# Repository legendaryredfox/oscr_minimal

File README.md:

# oscr_minimal — dumper de cartuchos SNES / NES / Famicom / Mega Drive / GBA

*English summary: [`README.en.md`](README.en.md).*

Shield para **Arduino Mega 2560 (R3)** que lê ROMs e saves de cartuchos pela USB, direto para o PC.
Sem LCD, sem cartão SD. Somente um cartucho por vez.

> **Estado:** 12 placas com projeto KiCad e gerbers, firmware (fork do OSCR com protocolo serial), CLI Python, CLI e GUI em Kotlin (pt-BR, en, ru, zh). **Nenhuma placa foi montada e nada foi testado com cartucho real**: só os testes automáticos no PC, as verificações de hardware abaixo e, em 2026-11-21, a primeira execução num Mega sem shield (`docs/referencia/teste-de-bancada.md`) rodaram. Ver "O que foi testado e o que falta".

## Atribuição

Baseado no **Open Source Cartridge Reader (OSCR)** de sanni e comunidade.

- Hardware original: <https://github.com/sanni/cartreader> (licença **CC BY 4.0**).
  Upstream atual: <https://github.com/oscartreader>.
- Firmware original: GPL v3. O firmware deste projeto continuará GPL v3.
- Slots (símbolos e footprints) copiados do OSCR, com alterações descritas em `boards/_lib/README.md`.

Adaptado por: <https://github.com/legendaryredfox/oscr_minimal>

## Diferenças em relação ao OSCR original

Este projeto não é uma reimplementação: o firmware é o do OSCR e as placas mantêm a pinagem dele. O que muda é **onde fica a interface** (no computador, não no aparelho) e **o tamanho do hardware**.

| | OSCR original | Este projeto |
|---|---|---|
| **Uso** | Aparelho independente: tela LCD, botão rotativo e cartão SD; o PC é opcional | Só com o computador: controle e arquivos pela USB. **Sem LCD, sem botões, sem cartão SD, sem RTC** |
| **Onde vão ROM e save** | Para arquivos no cartão SD | Direto para o PC por um protocolo serial binário (quadros com CRC32, blocos com ACK, 1.000.000 baud, com recuo para 500.000 e 115.200); o firmware nunca guarda arquivo |
| **Placa** | HW5: placa SMD com o módulo Mega Pro embutido e todos os slots | Shield **100 % THT** sobre um **Arduino Mega 2560 R3** comum, soldável à mão; várias variantes por combinação de sistemas (`boards/README.md`), da mínima de dois slots à completa |
| **Pinagem** | HW5 | **Idêntica**: cada sinal de cada slot vai para o mesmo pino do Mega, e por isso os núcleos de leitura do OSCR rodam sem alteração (`boards/<placa>/docs/pinmap.md` guarda a tabela cruzada com o OSCR) |
| **Tensão dos slots** | Chave 3,3 V / 5 V e VSELECT | 5 V fixo nos slots SNES, NES, Famicom, Mega Drive e Master System; 3,3 V nos slots GBA e N64 (regulador próprio). Algumas versões recentes de placa têm seletor 3,3 V / 5 V opcional, com trava por jumper. O 5 V **não** é desligado por software |
| **Relógio e CIC** | Si5351 e CIC conforme a versão da placa | Módulo Si5351 em header fêmea; CIC do SNES em PIC12F629 num soquete da própria placa (a alternativa com RP2040 está planejada e ainda não foi validada) |
| **Menus e botões** | Menus no LCD | O laço de comandos do protocolo (`firmware/oscr/src/dumper/`) chama as funções dos núcleos direto, **sem menu**; erros fatais e esperas por botão voltam ao laço em vez de travar |
| **Identificação do jogo** | Banco CRDB no SD | No PC: bases No-Intro e NES 2.0 (CRC32, SHA-1), busca e nome do arquivo pelo jogo (`--db`, `--game`) |
| **Segurança de gravação** | Pelo menu | O PC faz backup do save antes de gravar, relê e compara depois, pede confirmação e recusa tamanhos que não cabem no chip |
| **Interface** | Tela e botões | CLI em Python, CLI em Kotlin (mesmo contrato, saída JSON para scripts e agentes) e GUI em Kotlin para Linux, macOS e Windows (pt-BR, en, ru, zh) |
| **Gravar o firmware** | Ferramentas do upstream | `dumper firmware-flash` ou o cartão da GUI; com a placa escolhida o programa confere o firmware, grava o perfil da placa na EEPROM e, se faltar suporte, grava a imagem certa depois de pedir confirmação |

### Firmware: o que é do OSCR e o que é daqui

- **Base:** o firmware novo do OSCR (`vendor/oscr/firmware`), copiado para `firmware/oscr/`. Quem escolhe os núcleos é o `user.ini`: SNES (com Sufami Turbo, GPC, Satellaview e SF Memory), NES/Famicom, Mega Drive, Master System, N64, GB/GBC/GBA, programador de flash e o autoteste, mais 19 outros sistemas por adaptador no slot SNES (F-20: Atari 2600/5200/7800/8 bits/Lynx/Jaguar, ColecoVision, Neo Geo Pocket, Vectrex, Arcadia 2001, RCA Studio II, Tomy Pyuuta, Supervision, PV-1000, Bally Astrocade, Channel F, Odyssey 2, Pokémon Mini e V.Smile; adaptadores ainda não desenhados, `docs/planos/adaptadores.md`). Os outros consoles do upstream (por exemplo Commodore 64 e PC Engine) **não estão ligados** (`docs/planos/pendencias.md`).
- **Regra do projeto:** chamar a função do OSCR direto e escrever código próprio só nas costuras. Onde divergimos, o motivo está em `docs/decisoes.md`.
- **Código só daqui** (`firmware/oscr/src/dumper/`): o protocolo e a sessão; o `StreamFile`, arquivo virtual que no lugar do SD manda os bytes pela serial; o laço de comandos; o perfil da placa (`BOARD`, na EEPROM); o comando de tensão (`VOLT`); a calibração do Si5351 (`CLOCK`, guardada na EEPROM, no lugar do arquivo `snes_clk.txt` do SD); e o `SELFTEST`.
- **Remendos no upstream:** poucos e marcados com `OSCR_DUMPER` ou "fork": o tipo do arquivo e do `sd` em `Storage`, a UI de texto muda (`ClockedSerial.mute`), os tratamentos de erro e de `waitButton` do `ascii.cpp` e o `main.cpp` (laço próprio no lugar do menu).
- **Baud:** 1.000.000, contra 250.000 do upstream, definido pelo `monitor_speed` da placa `mega-embed` no `user.ini`.
- **Limites conhecidos do fluxo serial:** só existe leitura sequencial (sem `seek`), e o que o núcleo relê para conferir um save gravado devolve 0 bytes; por isso a conferência fica a cargo do PC, que relê depois de gravar.
- Mapa completo e estado: `docs/referencia/fork-oscr.md`. Cada função do OSCR e onde ela mora aqui: `docs/referencia/funcoes-oscr.md`.

### O que isto **não** substitui

- O OSCR original tem anos de uso e de cartuchos reais. **Este fork quase não tem validação em hardware:** em 2026-11-21 rodou pela primeira vez, num Mega sem shield e sem cartucho, e essa primeira execução achou e corrigiu vários problemas, de baud errado a gravação de firmware que travava (D196 a D199). **Nenhuma leitura de cartucho real foi feita ainda.** Os núcleos do OSCR são os de sempre, mas o que está em volta (protocolo, placas, sequência de chamadas) é novo.
- Quem quer um leitor autônomo, sem computador, deve usar o OSCR original.
- Funções do OSCR que ainda faltam aqui: `docs/referencia/funcoes-oscr.md`.

## Conteúdo

| Pasta | O que tem |
|---|---|
| `CLAUDE.md` | Decisões de projeto e fases (também serve de instrução para assistentes de código) |
| `boards/` | **Variantes de hardware**, uma pasta cada (índice e estado em `boards/README.md`). Com projeto KiCad e gerbers: `16_and_8_bits/` (5 slots), `16_bits/` (SNES e Mega Drive) e as de um sistema só ou de dois: `megadrive/`, `snes/`, `nes/`, `famicom/`, `famicom_nes/`, `8_bits/` (NES, Famicom e Master System), `gb_gba/`, `completa/` (sete slots) |
| `boards/<placa>/docs/pinmap.md` | **Fonte da verdade** de cada placa: pino do slot → pino do Mega (o da `16_and_8_bits` é gerado por `tools/gen_pinmap.py`; os das outras são recortes dele) |
| `docs/decisoes.md` | Log de decisões, desvios e pendências |
| `boards/<placa>/hardware-<versão>/` (uma pasta por versão), `fab/`, `docs/` | Projeto KiCad 10 (`dumper.kicad_pro/_sch/_pcb`), gerbers e zip da JLCPCB (`fab/PEDIDO.md` diz como pedir) e `bom.md`/`montagem.md` de cada placa |
| `boards/_lib/` | Símbolos e footprints KiCad compartilhados entre as variantes |
| `docs/referencia/uso.md` | **Guia de uso**: casos de uso, cenários por sistema e solução de problemas |
| `docs/referencia/protocolo.md`, `docs/referencia/cli.md`, `docs/referencia/fork-oscr.md`, `docs/referencia/funcoes-oscr.md`, `docs/referencia/limites.md` | Protocolo serial, guia da CLI, o que o fork muda no OSCR, inventário das funções do OSCR e limites conhecidos |
| `docs/planos/` | O que ainda não foi feito: `pendencias.md` (ids e o que falta), `adaptadores.md` (adaptadores da F-20), `melhorias-megadrive.md`, `placa-v1.3-rp2040.md` |
| `docs/planos/placa-v1.3-rp2040.md`, `firmware/cic_rp2040/` | CIC do SNES com RP2040-Zero no lugar do PIC (ainda não validado; as placas atuais usam o PIC12F629) |
| `firmware/`, `host/`, `gui/` | Comuns a todas as variantes |
| `database/oscr/` | Base de jogos (24 007, CRC32) do OSCR legado, GPL v3, mais `json/` (bases do `oscr-databases`, 4,9 mil CRC32 novos; o repositório de origem não declara licença, D127); carregada sozinha pelo host e pela GUI (D88, D127) |
| `tools/` | Scripts de hardware: `check_netlist.py` (`--board <placa>`), `export_fab.sh`, `gen_pinmap.py`, `build_lib.py`, `fill_zones.py` e os de cada placa (`megadrive/`, `snes/`, `nes/`, `famicom/`, `famicom_nes/`, `gb_gba/`, `revisao/`); ver `tools/README.md` |

## Adaptadores e repositórios de referência

O código de leitura dos cartuchos vem do OSCR; o que muda por sistema é o adaptador. Fontes consultadas e adaptadores que o firmware reconhece (D136, D137):

| Referência | Para quê |
|---|---|
| <https://github.com/sanni/cartreader> (pasta `hardware/`: `mastersystem_adapter`, `six_slot_adapter`, `*_adapter`) | KiCad dos adaptadores do OSCR; o slot Master System da `megadrive_sms` e os footprints dos slots vêm daí (CC BY 4.0). Arquivado desde 2026-06 |
| <https://github.com/oscartreader/oscr-firmware> | firmware atual do OSCR (GPL v3), base do fork em `firmware/oscr/` |
| <https://github.com/oscartreader/oscr-databases> | bases de jogos e a tabela de chips de flash (`database/oscr/`, D127 e D135; sem licença declarada) |
| <https://github.com/oscartreader/oscr-hardware> | repositório de hardware do novo upstream (vazio em 2026-11-08) |
| <https://github.com/sanni/cartreader/discussions/874> | discussão do adaptador de Game Gear (slot com o conector do RetroSix) |
| <https://www.raphnet.net/electronique/sms_cartridge_programmer/index_en.php> | adaptador **Raphnet** de Master System / SG-1000 (modo `SMSRaphnet` e `SG1000Raphnet` do `SMS.cpp`) |
| <https://forum.retrode.com> | adaptadores **Retrode** (`SMSRetrode`, `GGRetrode` do `SMS.cpp`) |
| <https://www.retrosix.wiki> | pinagem do cartucho de Game Gear e de outros consoles Sega |
| <https://www.smspower.org/maxim/Documents/Pinouts> | pinagem do conector de cartucho do Master System, Mark III e SG-1000 |

**Game Gear e SG-1000** não têm slot próprio nas placas deste projeto: usam adaptador no slot Mega Drive (Retron 3in1, Retrode, Raphnet). Os adaptadores que achei são comerciais; **não encontrei arquivos abertos** (KiCad) deles. Se aparecer um adaptador de código aberto, acrescente o link aqui.

**Tensão dos adaptadores (D138).** Os slots são de 5 V; os flashcarts comuns de Mega Drive e Master System precisam disso (regulam 3,3 V por dentro). As placas v1.1 de Mega Drive, SMS, NES e Famicom têm o **seletor 3,3 V/5 V** (padrão 5 V, `--voltage 3v3` para 3,3 V, alerta ao passar de 3,3 V para 5 V) e o jumper J1 \"TRAVA 3,3 V\"; todas as placas têm o fusível F1 (5×20 mm, 500 mA, em suporte de clipes, troca sem solda) opcional. Adaptador de Game Gear ou cartucho de 3,3 V: confira a tensão do adaptador antes de ligar. Detalhes: `docs/decisoes.md` D138.

## Aviso

- **Use por sua conta e risco.** Hardware e software saem sem garantia (CC BY 4.0 e GPL v3). Placas e firmware são experimentais.
- **Um cartucho por vez.** As placas levam 5 V aos slots de SNES, NES, Famicom, Mega Drive e Master System; os slots GBA e N64 são 3,3 V (regulador próprio), e as versões com seletor de tensão podem pôr o slot em 3,3 V. Desligue o USB antes de trocar de cartucho e **não use adaptador de GB/GBA** em placa sem o slot GBA.
- **Gravar ROM apaga o chip**, e abortar no meio deixa o chip pela metade. Faça backup do save antes de gravar e comece por cartuchos sem valor (`docs/referencia/uso.md`, seção 7).
- **Uso legal.** A ferramenta serve para fazer cópia de segurança dos cartuchos que você possui. Este repositório não distribui ROMs, BIOS nem chaves; `database/oscr/` só tem listas de nomes e CRC32 do OSCR.
- Nintendo, Super Nintendo, Famicom, Game Boy, Sega, Mega Drive e outros nomes são marcas dos seus donos, citadas só para dizer com o que o projeto é compatível. Sem vínculo com essas empresas nem com o projeto OSCR.

## O que foi testado e o que falta

Cobertura medida (Python 90 %, Kotlin 91,7 % das linhas, C++ puro no PC) e o que nenhum teste alcança: [`docs/referencia/cobertura-testes.md`](docs/referencia/cobertura-testes.md).

**Testado no PC (2026-11-27, D228):** host Python (`cd host && python3 -m pytest -q`, 478 testes), firmware (`make -C firmware/oscr/pc-tests test`, 26 binários de protocolo e regras puras; `pio run -e SerialASCII` compila, 77 % do flash), GUI e CLI Kotlin (`cd gui && ./gradlew :shared:jvmTest :desktopApp:compileKotlin :cliApp:compileKotlin`; a janela abre em display virtual, `tools/gui_smoke.sh`), as 12 placas em 22 versões (`python3 tools/check_all_boards.py`: ERC, DRC sem ligação aberta, netlist contra o `pinmap.md`, silk e SHA-256 dos zips; 0 erros na D191) e as tabelas dos adaptadores (`tools/check_adaptador_*.py`). O CI (`.github/workflows/ci.yml`) nunca executou.

**Em hardware:** só um Mega sem shield, sem Si5351 e sem cartucho (2026-11-21, D196 a D199: baud, gravação do firmware pela GUI, autoteste, perfil da placa). Cinco PIC12F629 gravados e conferidos por leitura, nenhum testado num cartucho (D214, D220).

**Falta:** montar uma placa e fazer o primeiro dump comparando o CRC32 com o No-Intro (roteiro na seção 7 de `docs/referencia/uso.md` e em `docs/referencia/teste-de-bancada.md`); conferir as medidas dos slots e do Si5351, o lado da etiqueta e os espaçadores com as peças reais; revisar à mão no KiCad os layouts do autoroteador; desenhar os adaptadores da F-20; serial a 1.000.000 baud em macOS e Windows; revisão das traduções ru e zh; dmg e msi. A única placa encomendada é a `16_bits` v1.0 original. Lista completa e o que falta do OSCR: `docs/planos/pendencias.md` e `docs/referencia/funcoes-oscr.md`.

## CIC do SNES: alternativas ao chip de 8 pinos

As placas com SNES usam hoje o **PIC12F629** (DIP-8, em soquete, gravado com o `snescic-lock-resync.hex` do OSCR). Estamos **estudando alternativas ao CIC de 8 pinos**; a mais avançada é um RP2040-Zero que roda o mesmo programa num interpretador (`docs/planos/placa-v1.3-rp2040.md`, `firmware/cic_rp2040/`, D89). Nada disso foi validado em hardware, e o PIC continua sendo o caminho suportado.

## Verificação

```
python3 tools/check_netlist.py --board <placa>        # netlist do esquemático vs boards/<placa>/docs/pinmap.md
kicad-cli sch erc boards/<placa>/hardware-<versão>/dumper.kicad_sch                # ERC
kicad-cli pcb drc --schematic-parity boards/<placa>/hardware-<versão>/dumper.kicad_pcb   # DRC
python3 tools/check_all_boards.py                     # todas as placas e versões de uma vez
tools/export_fab.sh <placa> <versão>                  # gerbers, furos, BOM e zip em boards/<placa>/fab/
```

## Recriar o `vendor/` (não versionado)

```
mkdir -p vendor/oscr && cd vendor/oscr
git clone --depth 1 https://github.com/sanni/cartreader legacy
git clone --depth 1 https://github.com/oscartreader/oscr-firmware firmware
```

`tools/gen_pinmap.py` lê `vendor/oscr/legacy/` (pinout.ods, esquemáticos KiCad, firmware).

## Contribuir

Veja `CONTRIBUTING.md`. Testes em hardware são o que mais ajuda: abra uma issue com o modelo "Teste em hardware" (placa, cartucho, versão, logs).

## Requisitos

KiCad 10.0.8 (`kicad-cli`), Python 3.11+. Para refazer layouts: o servidor MCP do KiCad (Python com `pcbnew`) e o Freerouting; ver `tools/README.md` e `docs/decisoes.md` (D92 a D101).

## Licença

Hardware: **CC BY 4.0**. Software: **GPL v3 ou posterior**. Mesmas licenças do OSCR; ver `LICENSE.md`.

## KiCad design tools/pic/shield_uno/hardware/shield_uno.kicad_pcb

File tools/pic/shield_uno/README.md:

# Programador de PIC12F629 em shield para Arduino Uno

Grava o **PIC12F629** (o CIC "lock" do SNES SA-1, `snescic-lock-resync.hex`) com um Arduino Uno e o
[ardpicprog](https://rweather.github.io/ardpicprog/). Resolve o problema de quem não tem PICkit: o 12F629 só grava
com Vpp de uns 12 a 13 V no MCLR, e o CH341A não gera isso.

Este shield é o circuito do ardpicprog para o PIC12F629 em DIP-8 direto (a ligação já descrita em
[`../uno/README.md`](../uno/README.md), D91), desenhado em KiCad. Há três jeitos de montar o mesmo circuito, na ordem
de comodidade: **A.** PCB do shield (este projeto KiCad), **B.** protoboard, **C.** placa perfurada.

> **Estado (2026-11-25):** v1.1 (pinos D8/D9/D10). **Nada foi encomendado**, e nem esta PCB nem os layouts de protoboard e de
> placa perfurada desenhados aqui foram montados. O circuito foi usado em bancada numa montagem própria em placa perfurada
> (cinco PICs gravados, D214 e D220). Conferido no PC: ERC do esquemático
> sem avisos, DRC da PCB sem violações e sem pontos soltos, netlist da PCB contra a tabela de ligações do ardpicprog
> (`scripts/check_netlist.py`), e os desenhos da protoboard e da placa perfurada (`scripts/protoboard.py`,
> `scripts/perfboard.py`). A pinagem do Uno é a do footprint do Mega no projeto, cotas oficiais do Arduino; não foi
> medida num Uno real. O limite máximo de Vpp do 12F629 (DS41191) **não foi conferido**: meça o MCLR antes de pôr o chip.

## Sem diodo por padrão (D1 é DNP)

**O padrão é montar SEM o diodo D1.** O circuito original do ardpicprog não tem diodo, e assim não se perdem 0,2 a
0,3 V de Vpp. Em cada montagem:

| Montagem | Padrão (sem D1) | Se quiser o diodo |
|---|---|---|
| **A. PCB** | D1 **não montado** (DNP) e **JP1 fechado**: jumper (shunt), fio ou gota de solda entre os dois pinos de JP1 | montar D1 (faixa = K para o lado do circuito) e **abrir** JP1 |
| **B. Protoboard** | o positivo da fonte vai direto ao trilho "+" | ver "Com o diodo" na seção B |
| **C. Placa perfurada** | fio de ponte de E2 a I2, no lugar do diodo | tirar a ponte e soldar o diodo em E2 (anodo) e I2 (catodo) |

**Risco de ficar sem ele:** não há proteção contra a fonte ligada ao contrário (plugue com polaridade trocada,
adaptador de centro negativo). Os caminhos passam por R1 (10 kΩ), R2 (4,7 kΩ) e R4 (1 kΩ), então as correntes ficam
em miliampères e nada deve pegar fogo, mas pode queimar o LED vermelho (tensão reversa de ~5 V), o BC547 ou o
PIC (o MCLR conduz ~1 mA pelo diodo interno do pino; não conferi o limite no datasheet). **Antes de ligar, confira a
polaridade da fonte com o multímetro.** O bloqueio de D1 é a única proteção que a placa tem para isso; se a polaridade
do seu plugue é conhecida e marcada, dispensá-lo é razoável. Se o Vpp medido no MCLR ficar **perto do limite baixo**
(não conferi o DS41191), o certo é ficar sem o diodo.

Esquemático (para quem sabe ler): [`docs/esquematico.pdf`](docs/esquematico.pdf). Para todo mundo, o **mapa das ligações** logo abaixo.

## Mapa das ligações (para qualquer pessoa seguir)

<!-- mapa -->

Lista **fio a fio** (faça um traço em cada fio que montar). Os fios pretos vão todos ao **GND**; o resto liga duas peças:

| Feito | Cor do fio | De | Para |
|:-:|---|---|---|
| ☐ | **preto** | GND do Uno | trilho preto de GND |
| ☐ | **preto** | pino 8 do chip | trilho preto de GND |
| ☐ | **preto** | capacitor C1 (perna de baixo) | trilho preto de GND |
| ☐ | **preto** | emissor (E) do BC547 | trilho preto de GND |
| ☐ | **preto** | LED vermelho (perna curta) | trilho preto de GND |
| ☐ | **preto** | LED amarelo (perna curta) | trilho preto de GND |
| ☐ | **preto** | negativo (−) da fonte | trilho preto de GND |
| ☐ | **laranja** | D8 do Uno | pino 1 do chip e perna de cima do capacitor C1 |
| ☐ | **verde** | D9 do Uno | pino 6 do chip |
| ☐ | **azul** | D10 do Uno | pino 7 do chip |
| ☐ | **rosa** | pino 4 do chip (MCLR) | resistor R1 (10 kΩ) e coletor (C) do BC547 |
| ☐ | **roxo** | A1 do Uno | resistor R2 (4,7 kΩ), e dele à base (B) do BC547 |
| ☐ | **amarelo** | A5 do Uno | resistor R3 (220 Ω), e dele à perna longa (+) do LED amarelo |
| ☐ | **vermelho** | positivo (+) da fonte | resistor R1 (o outro lado dele) e resistor R4 (1 kΩ), e dele à perna longa (+) do LED vermelho |

Os pinos 2, 3 e 5 do chip **não levam fio**. O desenho (`docs/esquema-simples.svg` e `.png`) sai de `scripts/esquema_simples.py`, que confere cada fio contra a tabela de ligações do verificador (`protoboard.py`) e para com erro se algum fio ligar o que não deve.
<!-- /mapa -->

## Como funciona

```
13 V (+) ──► [D1 1N5819: DNP, ponte] ─┬── R1 10 kΩ ──┬── PIC pino 4 (MCLR)
                                        │              └── coletor do Q1 (BC547)
                                        └── R4 1 kΩ ── LED vermelho ── GND  (acende = há 13 V)
Uno A1 ── R2 4,7 kΩ ── base do Q1        emissor do Q1 ── GND
Uno D8  ── PIC pino 1 (Vdd)              100 nF entre o pino 1 e o GND, junto ao chip
Uno D9  ── PIC pino 6 (clock)
Uno D10 ── PIC pino 7 (dados)
Uno A5 ── R3 220 Ω ── LED amarelo ── GND (atividade)
Uno GND ── PIC pino 8 ── GND da fonte de 13 V   (GND comum!)
PIC pinos 2, 3 e 5: sem ligação
```

- A1 em nível **baixo** corta o BC547 e deixa o MCLR em ~13 V (gravação); em nível alto o BC547 puxa o
  MCLR a GND (reset). O sketch aplica os 13 V **antes** de ligar o Vdd.
- **O sketch precisa do patch de pinos.** O `ProgramPIC.pde` do ardpicprog usa `PIN_VDD 2`, `PIN_CLOCK 4` e `PIN_DATA 7`;
  este projeto usa 8, 9 e 10 (`PIN_MCLR A1` e `PIN_ACTIVITY A5` iguais). O instalador aplica o patch por padrão
  ([`../uno/README.md`](../uno/README.md)). Até a v1.0 o shield usava D2/D4/D7 (D221).
- Os 13 V nunca vão a um pino do Uno. O PIC é alimentado pelo pino D8 do Uno (consumo de poucos mA).
- **D1 (1N5819) é opcional e vem desmontado (DNP)**; veja "Sem diodo por padrão" acima. Ele é um acréscimo deste
  projeto, o circuito original não tem. Na PCB, JP1 fica em paralelo com ele: fechado = sem diodo.
- A placa também tem um cabeçalho ICSP (J2, ordem do PICkit: 1 MCLR, 2 Vdd, 3 GND, 4 dados, 5 clock) e três pontos de
  teste (MCLR, VDD, GND) para o multímetro.

## Material

| Qtd | Peça | Ref. na PCB | Observação |
|---|---|---|---|
| 1 | Arduino Uno R3 + cabo USB | | clone com CH340 serve (aparece como `/dev/ttyUSB0`) |
| 1 | Fonte de 13 V, ≥ 100 mA, **regulada** | | meça em vazio antes (veja "Antes de ligar") |
| 1 | PIC12F629-I/P (DIP-8) virgem ou a regravar | U1 | em soquete DIP-8 |
| 1 | Soquete DIP-8 | U1 | de contato torneado, para trocar de chip muitas vezes |
| 1 | Transistor NPN BC547 | Q1 | substitutos: BC548, 2N3904, 2N2222; pinagem abaixo |
| 0 (1 se quiser) | Diodo 1N5819 | D1 | **opcional, DNP**: só se for usar a proteção contra fonte invertida |
| 1 | Barra de 2 pinos 2,54 mm + jumper (shunt) | JP1 | só na PCB; fechado = sem D1. Pode ser um fio ou solda |
| 1 | Resistor 10 kΩ | R1 | 1/4 W |
| 1 | Resistor 4,7 kΩ | R2 | |
| 1 | Resistor 220 Ω | R3 | |
| 1 | Resistor 1 kΩ | R4 | |
| 1 | Capacitor cerâmico 100 nF | C1 | |
| 1 | LED vermelho 3 mm | D2 | indica os 13 V |
| 1 | LED amarelo 3 mm | D3 | atividade |
| 1 | Borne de parafuso 5,08 mm, 2 vias | J1 | entrada da fonte; para um plugue P4 use um adaptador "jack fêmea com borne" |
| 1 | Barra de 6 pinos 2,54 mm | J2 | ICSP, opcional |
| 3 | Ponto de teste (pino ou argola) | TP1 a TP3 | opcional |
| 4 | Barras fêmea empilháveis do Uno (6, 8, 8 e 10 pinos) | A1 | só na PCB do shield |

**Pinagem do BC547.** TO-92, lado chato para você, pernas para baixo: C, B, E da esquerda para a direita (BC548
igual). Nos substitutos 2N3904 e 2N2222: E, B, C. Na PCB o footprint é C, B, E; um 2N3904 entra **virado
180°** (lado chato para o lado oposto ao do desenho) e assim as pernas caem certas. Na dúvida, modo diodo do multímetro: a base mede cerca de
0,6 V para as outras duas pernas com o "+" na base (NPN).

## Antes de ligar (vale para as três montagens)

1. **Meça a fonte de 13 V com o multímetro, sem carga.** Adaptadores "13 V" sem regulagem passam de 15 V em vazio.
   Alvo: cerca de 13 V no MCLR com o chip fora. Confira o Vpp máximo do 12F629 no DS41191 antes de pôr o chip.
2. **Confirme a polaridade da fonte com o multímetro** (+ no centro ou na lateral). Sem o diodo D1 (o padrão) nada
   protege contra polaridade invertida.
3. Sem o PIC no soquete, ligue só a fonte: o LED vermelho acende. Meça o **MCLR** (TP1 na PCB; pino 4 do soquete):
   com o Uno em reset (A1 alto) fica perto de 0 V; com A1 solto, ~13 V.
4. Só então ponha o PIC (entalhe/pino 1 conforme o desenho) com tudo **desligado**; ligue a fonte por último e
   desligue-a primeiro.
5. Feche o monitor serial da IDE antes de ler ou gravar (ele roubaria a porta).

## A. PCB do shield (`hardware/`)

Placa de 2 camadas, 52,6 × 53,3 mm, 100% THT, que encaixa nos headers do Uno. O lado esquerdo (conector USB-B e jack
do Uno) fica livre de propósito.

- Projeto: `hardware/shield_uno.kicad_pro` (KiCad 9 ou 10). Fabricação: `fab/shield_uno-v1.1-jlcpcb.zip` (gerbers e
  furos, 2 camadas, 1,6 mm, HASL) e `fab/bom.csv`. **Nada foi encomendado.**
- Montagem, do mais baixo ao mais alto:
  1. resistores (R1 a R4) e capacitor C1; **D1 não se monta** (DNP). Feche o **JP1** com um jumper, fio ou solda
     (se quiser o diodo: monte D1, com a faixa para o lado do K, e deixe o JP1 aberto);
  2. soquete DIP-8 (entalhe para o lado do pino 1, desenhado na serigrafia);
  3. LEDs (perna curta = K, lado do quadrado) e BC547;
  4. cabeçalho ICSP, pontos de teste e borne;
  5. por último as barras empilháveis, **com o shield encaixado no Uno** para alinhar.
- **Corte as pernas rente** na face de baixo: o Uno tem o ATmega328P e outras peças ali embaixo. Se sobrar perna,
  cubra com fita isolante.
- O borne J1 fica no canto de baixo à esquerda: `+` do lado da borda esquerda, `GND` ao lado.
- Para refazer os arquivos a partir dos scripts: veja "Arquivos".

## B. Protoboard (830 pontos)

Montagem **passo a passo, com um desenho para cada passo**, feita para quem nunca montou um circuito: em cada figura o que
**acabou de entrar** aparece com um brilho amarelo e etiquetas com o nome do furo. Os fios saem do Uno por seis pinos; as
cores dos fios ajudam a não errar.

Os desenhos e as tabelas desta seção são gerados por `scripts/protoboard_desenho.py` a partir de `scripts/protoboard.py`, que
**confere** que cada fio e cada peça ligam exatamente os pontos certos (sem curtos). Para refazê-los: `python3 scripts/protoboard_desenho.py` (precisa do `google-chrome` ou `chromium` para os PNG).

<!-- protoboard -->
### O que você precisa (confira antes de começar)

| Peça | Quantas | Como reconhecer |
|---|---|---|
| Protoboard de 830 pontos (a de 400 também serve) | 1 | com 2 trilhos no alto: um `+` (vermelho) e um `−` (azul) |
| PIC12F629 em soquete DIP-8 | 1 | chip preto de 8 pernas, com uma marca (ponto ou entalhe) no pino 1 |
| Transistor BC547 | 1 | 3 pernas; tem um lado chato |
| Resistor 10 k | 1 | faixas: **marrom, preto, laranja**, dourado |
| Resistor 4,7 k | 1 | faixas: **amarelo, violeta, vermelho**, dourado |
| Resistor 1 k | 1 | faixas: **marrom, preto, vermelho**, dourado |
| Resistor 220 Ω | 1 | faixas: **vermelho, vermelho, marrom**, dourado |
| Capacitor 100 nF | 1 | disquinho pequeno marcado **104** |
| LED vermelho e LED amarelo | 1 de cada | a perna **longa** é o `+` |
| Fios (jumpers) macho-macho | 11 | cores: preto 6, vermelho 2, laranja, azul, verde, roxo, amarelo (1 de cada; as cores ajudam, não são obrigatórias) |
| Fios macho-fêmea para o Uno | 6 | um para cada pino do Uno: GND, D8, D9, D10, A1, A5 |
| Fonte de 13 V e multímetro | 1 | para a medição antes de ligar |

### Os 6 pinos do Uno

| Pino do Uno | Cor do fio | Vai para | Para que serve |
|---|---|---|---|
| **D8** | laranja | furo c10 (pino 1 do PIC) | dá energia ao PIC (5 V) |
| **D9** | verde | furo j12 (pino 6 do PIC) | clock da gravação |
| **D10** | azul | furo j11 (pino 7 do PIC) | dados da gravação |
| **A1** | roxo | furo d18 (resistor de 4,7 k) | liga e desliga os 13 V no MCLR |
| **A5** | amarelo | furo j24 (resistor de 220) | acende o LED amarelo enquanto grava |
| **GND** | preto | trilho − | terra comum |

**Como ler os furos:** cada furo tem uma **letra** (linha, a a j) e um **número** (coluna 7 a 30). Exemplo: **c10** é a linha `c` na coluna `10`. As letras `a b c d e` ficam na metade de baixo e `f g h i j` na de cima; furos com o mesmo número **e na mesma metade** estão ligados entre si por dentro da protoboard.

**Regra de ouro:** nada ligado na tomada nem no USB enquanto você monta. A fonte só vai no passo 9.

#### Passo 1: Fio de GND do Uno

| O que | Onde |
|---|---|
| fio **preto** (GND do Uno) | do **Uno GND** ao trilho - |

> Todo o circuito precisa do mesmo GND do Uno.

#### Passo 2: O chip PIC12F629

| O que | Onde |
|---|---|
| **PIC12F629 no soquete DIP-8** | pino 1 em **e10**; pinos 1 a 4 em e10 a e13, pinos 8 a 5 em f10 a f13 |
| fio **preto** (pino 8 do PIC ao GND) | do furo **j10** ao trilho **-** |

> O PIC fica a cavaleiro do vao do meio, com o pino 1 em e10 (o entalhe do chip aponta para a esquerda).

#### Passo 3: Energia do chip

| O que | Onde |
|---|---|
| **Capacitor 100 nF (marcado 104)** | 1 em **b10**, 2 em **b8** |
| fio **laranja** (D8 do Uno: alimenta o PIC) | do **Uno D8** ao furo **c10** |
| fio **preto** (capacitor ao GND) | do furo **e8** ao trilho **-** |

> O capacitor fica junto do pino 1, perto do chip.

#### Passo 4: Dados e clock

| O que | Onde |
|---|---|
| fio **azul** (D10 do Uno: dados) | do **Uno D10** ao furo **j11** |
| fio **verde** (D9 do Uno: clock) | do **Uno D9** ao furo **j12** |

#### Passo 5: BC547 e resistor de 10 k

| O que | Onde |
|---|---|
| **Transistor BC547** | C em **a13**, B em **a14**, E em **a15** |
| **Resistor 10 k** (faixas marrom, preto, laranja, dourado) | 1 em **c13**, 2 em **c17** |
| fio **preto** (emissor do BC547 ao GND) | do furo **e15** ao trilho **-** |
| fio **vermelho** (13 V para o resistor de 10 k e para o LED) | do furo **e17** ao trilho **+** |

> O BC547 entra com o lado CHATO virado para voce (para a borda de baixo da figura): C, B, E da esquerda para a direita.

#### Passo 6: Comando do BC547

| O que | Onde |
|---|---|
| **Resistor 4,7 k** (faixas amarelo, violeta, vermelho, dourado) | 1 em **e18**, 2 em **e14** |
| fio **roxo** (A1 do Uno: comanda o BC547) | do **Uno A1** ao furo **d18** |

#### Passo 7: LED vermelho (tem 13 V)

| O que | Onde |
|---|---|
| **Resistor 1 k** (faixas marrom, preto, vermelho, dourado) | 1 em **a17**, 2 em **a21** |
| **LED vermelho** | A em **b21**, K em **b22** |
| fio **preto** (LED vermelho ao GND) | do furo **e22** ao trilho **-** |

> A perna LONGA do LED e o +; ela vai no furo de numero menor.

#### Passo 8: LED amarelo (atividade)

| O que | Onde |
|---|---|
| **Resistor 220** (faixas vermelho, vermelho, marrom, dourado) | 1 em **g24**, 2 em **g28** |
| **LED amarelo** | A em **h28**, K em **h29** |
| fio **amarelo** (A5 do Uno: luz de atividade) | do **Uno A5** ao furo **j24** |
| fio **preto** (LED amarelo ao GND) | do furo **i29** ao trilho **-** |

> A perna LONGA do LED e o +; ela vai no furo de numero menor.

#### Passo 9: Fonte de 13 V (por ultimo!)

| O que | Onde |
|---|---|
| fio **vermelho** (positivo da fonte de 13 V) | do **fonte +** ao trilho + |
| fio **preto** (negativo da fonte de 13 V) | do **fonte -** ao trilho - |

> Fonte DESLIGADA e polaridade conferida com o multimetro.

#### Pronto: confira

Com o multímetro em **continuidade (bip)** e **tudo desligado**:

| Meça entre | Deve dar |
|---|---|
| trilho `+` e trilho `−` | **sem** bip (senão há um curto) |
| trilho `−` e o pino 8 do PIC (furo f10) | bip |
| furo e13 (pino 4 do PIC) e furo a13 (coletor do BC547) | bip |
| furo c10 (D8) e furo e10 (pino 1 do PIC) | bip |

**Depois:** siga "Antes de ligar" (medir o MCLR com o chip fora) e "Gravar".

**Com o diodo (opcional, D1).** Tire o fio vermelho que vai do positivo da fonte ao trilho `+`. Ponha o diodo 1N5819 na fileira `c`: o lado **sem faixa** (anodo) em **c29** e o lado **com faixa** (catodo) em **c25**. Depois: um fio vermelho do **positivo da fonte** ao furo **c29**, e outro fio vermelho do furo **c25** ao trilho `+`. (O desenho acima não mostra isso.)
<!-- /protoboard -->

## C. Placa perfurada

Placa de furos a 2,54 mm de **22 colunas × 14 linhas** (uma de 5 × 7 cm serve), com um **cabo Dupont fêmea-fêmea de 6
vias** do barramento J3 ao Uno. Fios **isolados** (kynar/wire-wrap) no lado da solda; só o trilho de GND (linha N) pode
ser fio nu. Os furos têm nome: letra da linha (A a N) e número da coluna (1 a 22).

- Desenho gerado por `scripts/perfboard.py`, que **verifica** que cada fio liga exatamente os pontos certos e que não
  há curto. Tabelas completas de furos e fios: [`docs/perfboard.md`](docs/perfboard.md).
- A figura mostra o lado dos componentes visto de cima, com os fios do lado de baixo vistos por transparência.

Ordem de montagem:

1. Soldar o **soquete DIP-8** (colunas 13 e 16, linhas D a G; entalhe para cima = pino 1 em D13), os resistores, o
   capacitor, os LEDs, o BC547, o borne J1 e a barra J3 (furos A5 a A10, da esquerda para a direita: GND, D8, D9, D10, A1, A5),
   nos furos da tabela [`docs/perfboard.md`](docs/perfboard.md).
2. Passar os fios **na ordem da tabela de fios**, um a um, soldando as pontas e riscando na tabela. Os fios podem
   passar por cima de furos ocupados desde que sejam isolados; o trilho de GND (N5 a N21) é um fio nu soldado nos pontos
   marcados.
3. Conferir com o multímetro, tudo desligado: GND (J3 GND) com o pino 8 do soquete, o emissor do BC547 e os dois
   catodos; 13 V **sem** continuidade com o GND.
4. Ligar o cabo Dupont: J3 GND, D8, D9, D10, A1, A5 aos mesmos pinos do Uno (nesta ordem na barra, da esquerda para a
   direita). Siga "Antes de ligar" e "Gravar".

**D1 não é montado (DNP):** no lugar dele há um fio de ponte de **E2 a I2** (coluna 2). Para usar o diodo, tire esse fio
e solde o D1 com o anodo em E2 e o catodo (faixa) em I2; o fio de C2 a E2 continua.

Os pontos de teste e o ICSP ficam de fora nesta versão (o MCLR se mede no pino 4 do soquete).

## Gravar

O Uno precisa do sketch `ProgramPIC` do ardpicprog **com os patches deste repositório**, e o PC usa o `pic_texto.py`.
Instalação em [`../uno/README.md`](../uno/README.md). Resumo, com o shield montado e o PIC no soquete:

```
H=firmware/cic_rp2040/third_party/snescic-lock-resync.hex
python3 tools/pic/pic_texto.py ler backup.hex          # antes de tudo; guarde (OSCCAL e bits BG de fábrica)
python3 tools/pic/pic_texto.py gravar $H               # grava e confere
python3 tools/pic/pic_texto.py conferir $H
```
Não use `ardpicprog --erase` nem `--burn` com este sketch (D214, D220).

## Problemas

- **LED vermelho apagado:** fonte desligada, ou R4/LED ao contrário. Se a fonte puder estar invertida e não há D1, **desligue já** e meça a polaridade.
- **Não detecta o chip:** confira se o sketch usa D8/D9/D10, o pino 1 do PIC, o GND comum entre fonte e Uno, os contatos e
  se há ~13 V no pino 4 com A1 solto.
- **13 V não chegam ao MCLR:** BC547 com a pinagem errada (veja "Pinagem do BC547") ou R1 solto.
- **Erro de verificação:** grave de novo; se repetir, queda da fonte sob carga ou mau contato (na protoboard).
- **Nada na serial:** feche o monitor serial; confira a porta e o grupo `dialout`.

## Arquivos

| Caminho | O que é |
|---|---|
| `hardware/` | projeto KiCad (`shield_uno.kicad_pro/_sch/_pcb`), símbolo e footprint do Uno (`uno_shield.*`) |
| `fab/` | gerbers, furos, `bom.csv` (sem o D1, que é DNP) e o zip da JLCPCB |
| `docs/` | esquemático em PDF, mapa das ligações, imagem da placa, passos da protoboard, desenho e tabelas da placa perfurada |
| `scripts/gerar_sch.py` | gera o esquemático e o símbolo do Uno |
| `scripts/gerar_pcb.py`, `scripts/rotear.py` | geram a PCB (footprints, nets, contorno) e roteiam com o Freerouting, depois zonas de GND |
| `scripts/check_netlist.py` | confere a PCB contra a tabela do ardpicprog (usa `pcbnew`) |
| `scripts/exportar_fab.sh` | gerbers, furos, BOM e zip |
| `scripts/perfboard.py`, `scripts/protoboard.py`, `scripts/protoboard_desenho.py` | desenho e verificação das montagens B e C (a protoboard sai em passos, com PNG feitos pelo Chrome sem janela) |
| `scripts/esquema_simples.py` | o mapa das ligações (`docs/esquema-simples.svg/.png`) e a lista fio a fio do README; confere cada fio contra `protoboard.ESPERADO` |

Para refazer: `python3 scripts/gerar_sch.py`, depois, com o Python do venv do KiCad MCP (tem `pcbnew`),
`gerar_pcb.py`, `rotear.py` (precisa de `java` e `~/.kicad-mcp/freerouting.jar`) e `check_netlist.py`;
`kicad-cli sch erc` e `kicad-cli pcb drc --schematic-parity` conferem os arquivos.

## Licença e créditos

O circuito é do **ardpicprog**, de Rhys Weatherley (circuitos e documentação **CC BY-SA 2.5**,
https://rweather.github.io/ardpicprog/). Este shield é derivado dele e fica sob **CC BY-SA 2.5**. O firmware do Uno
(`ProgramPIC.pde`) e o programa do PC são GPL v3 e não estão neste repositório (o instalador baixa do upstream).

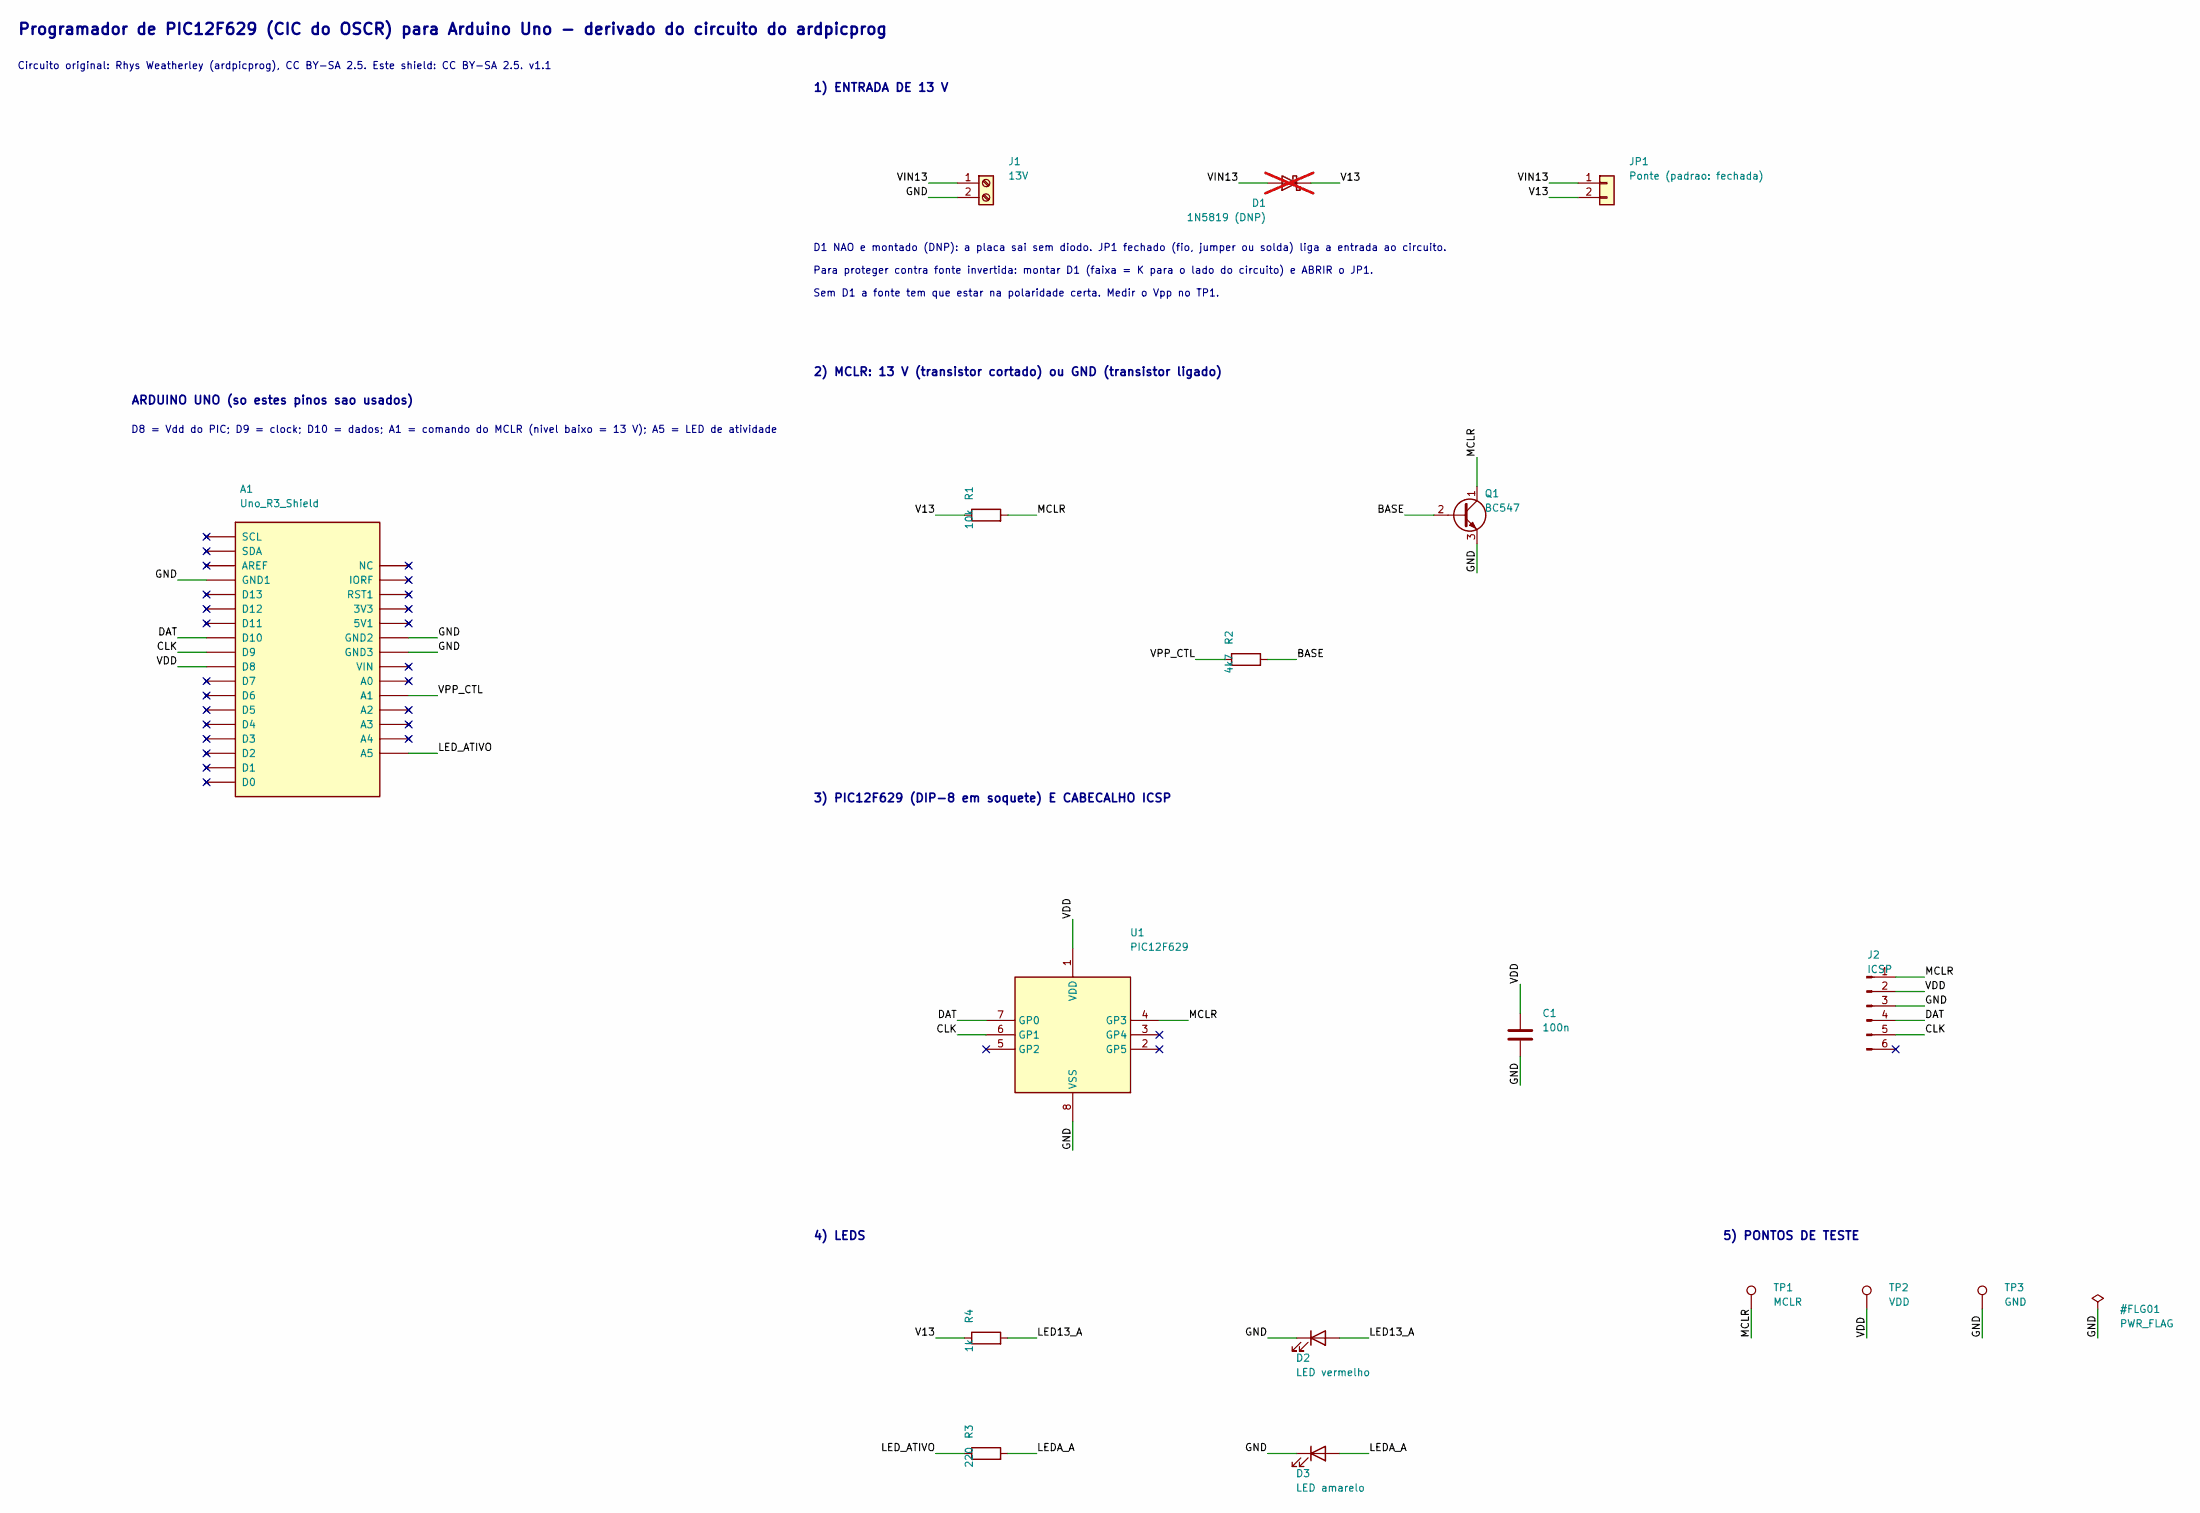
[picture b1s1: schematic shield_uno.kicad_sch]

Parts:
A1: Uno_R3_Shield
C1: 100n; C_Disc_D5.0mm_W2.5mm_P5.00mm
D1: 1N5819 (DNP); D_DO-41_SOD81_P10.16mm_Horizontal; not fitted
D2: LED vermelho; LED_D3.0mm
D3: LED amarelo; LED_D3.0mm
J1: 13V; TerminalBlock_Phoenix_MKDS-1,5-2-5.08_1x02_P5.08mm_Horizont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
J2: ICSP; PinHeader_1x06_P2.54mm_Vertical
JP1: Ponte (padrao: fechada); PinHeader_1x02_P2.54mm_Vertical
Q1: BC547; TO-92_Inline_Wide
R1: 10k; R_Axial_DIN0207_L6.3mm_D2.5mm_P10.16mm_Horizontal
R2: 4k7; R_Axial_DIN0207_L6.3mm_D2.5mm_P10.16mm_Horizontal
R3: 220; R_Axial_DIN0207_L6.3mm_D2.5mm_P10.16mm_Horizontal
R4: 1k; R_Axial_DIN0207_L6.3mm_D2.5mm_P10.16mm_Horizontal
TP1: MCLR; TestPoint_THTPad_D2.0mm_Drill1.0mm
TP2: VDD; TestPoint_THTPad_D2.0mm_Drill1.0mm
TP3: GND; TestPoint_THTPad_D2.0mm_Drill1.0mm
U1: PIC12F629; DIP-8_W7.62mm_Socket

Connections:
/BASE: Q1.2 (B), R2.2
/CLK: A1.D9, J2.5, U1.6 (GP1)
/DAT: A1.D10, J2.4, U1.7 (GP0)
/GND: A1.GND1, A1.GND2, A1.GND3, C1.2, D2.1 (K), D3.1 (K), J1.2, J2.3, Q1.3 (E), TP3.1, U1.8 (VSS)
/LED13_A: D2.2 (A), R4.2
/LEDA_A: D3.2 (A), R3.2
/LED_ATIVO: A1.A5, R3.1
/MCLR: J2.1, Q1.1 (C), R1.2, TP1.1, U1.4 (GP3)
/V13: D1.1 (K), JP1.2, R1.1, R4.1
/VDD: A1.D8, C1.1, J2.2, TP2.1, U1.1 (VDD)
/VIN13: D1.2 (A), J1.1, JP1.1
/VPP_CTL: A1.A1, R2.1

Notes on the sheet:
ARDUINO UNO (so estes pinos sao usados)
D8 = Vdd do PIC; D9 = clock; D10 = dados; A1 = comando do MCLR (nivel baixo = 13 V); A5 = LED de atividade
1) ENTRADA DE 13 V
D1 NAO e montado (DNP): a placa sai sem diodo. JP1 fechado (fio, jumper ou solda) liga a entrada ao circuito.
Para proteger contra fonte invertida: montar D1 (faixa = K para o lado do circuito) e ABRIR o JP1.
Sem D1 a fonte tem que estar na polaridade certa. Medir o Vpp no TP1.
2) MCLR: 13 V (transistor cortado) ou GND (transistor ligado)
3) PIC12F629 (DIP-8 em soquete) E CABECALHO ICSP
4) LEDS
5) PONTOS DE TESTE
Programador de PIC12F629 (CIC do OSCR) para Arduino Uno - derivado do circuito do ardpicprog
Circuito original: Rhys Weatherley (ardpicprog), CC BY-SA 2.5. Este shield: CC BY-SA 2.5. v1.1

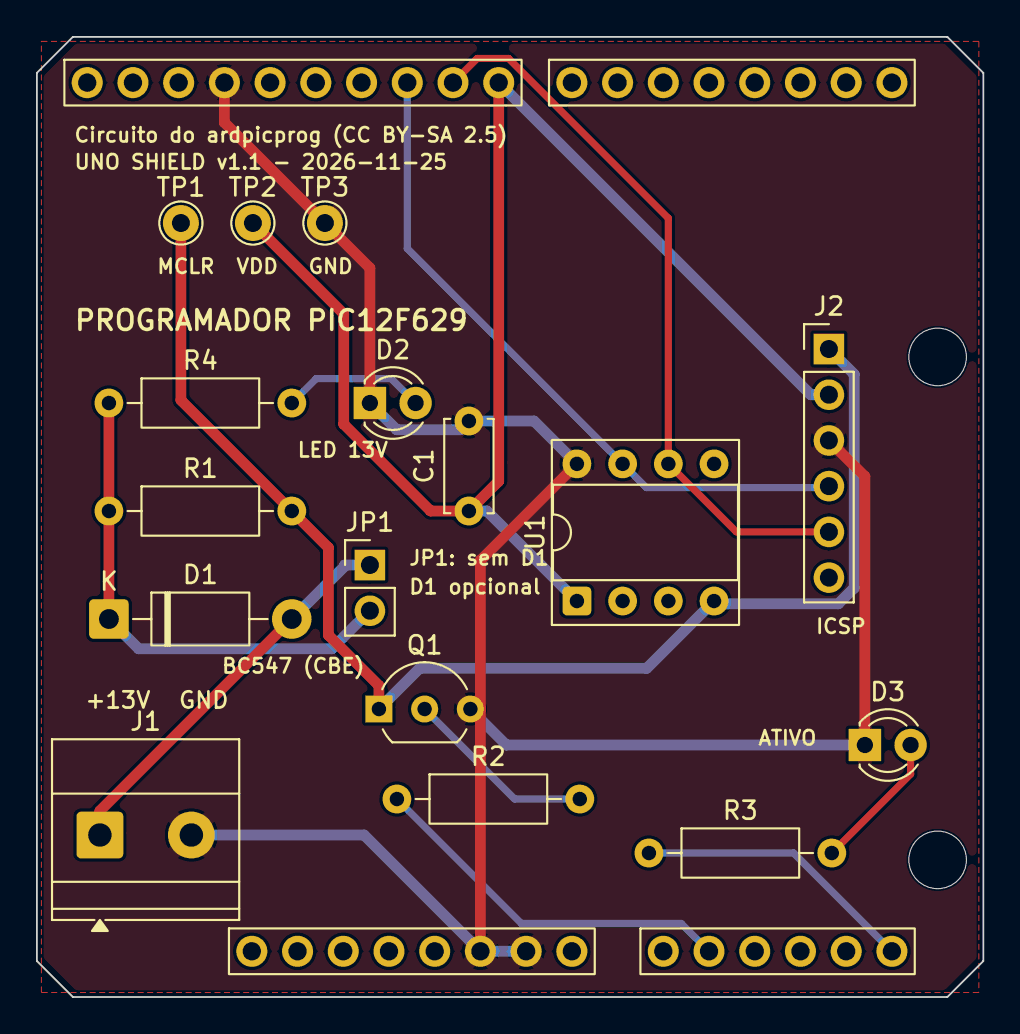
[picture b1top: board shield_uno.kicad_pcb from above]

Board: 2 copper layers, 52.6 x 53.3 mm, 17 parts (0 on the bottom side), 12 nets.

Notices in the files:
tools/gen_pinmap.py:
SPDX-License-Identifier: GPL-3.0-or-later
tools/pic/shield_uno/hardware/shield_uno.kicad_pcb:
Circuito: ardpicprog (R. Weatherley), CC BY-SA 2.5
Circuito do ardpicprog (CC BY-SA 2.5)
